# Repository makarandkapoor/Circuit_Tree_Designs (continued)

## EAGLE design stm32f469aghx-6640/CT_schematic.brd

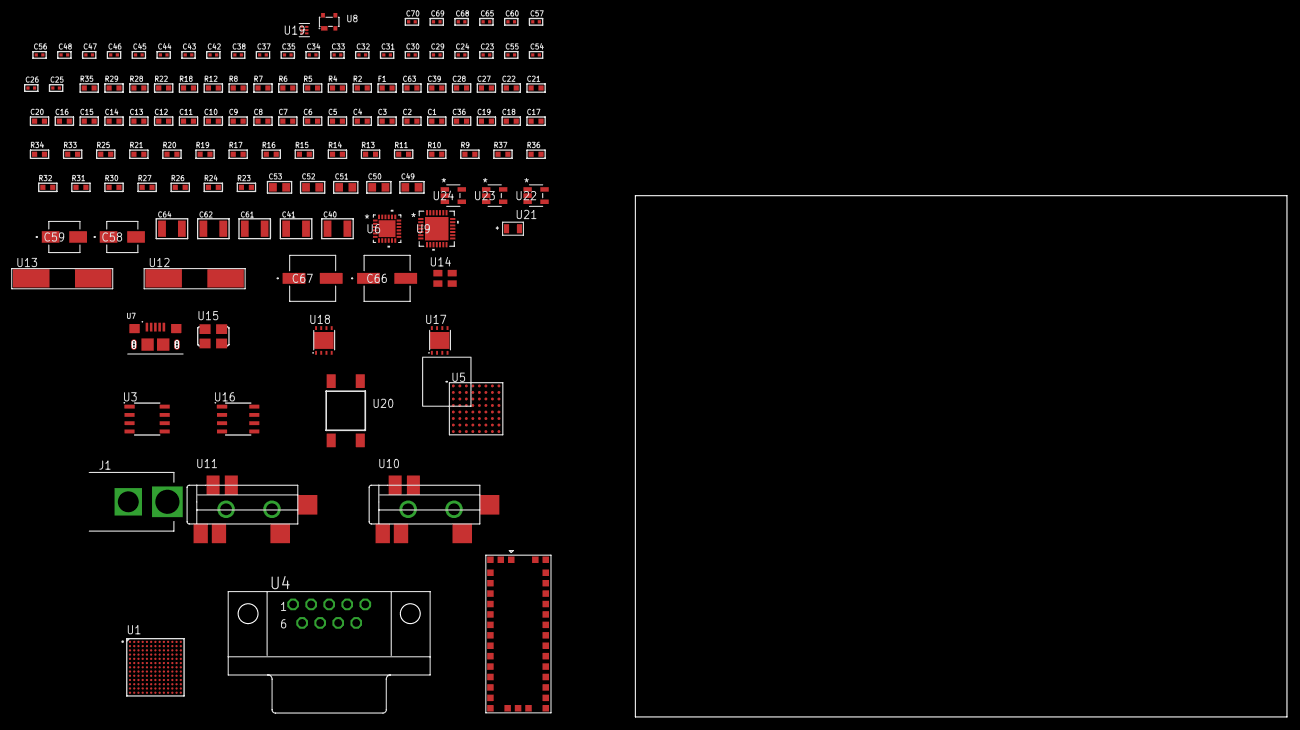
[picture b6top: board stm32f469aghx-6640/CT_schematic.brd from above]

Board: 2 copper layers, 131 parts (0 on the bottom side), 114 nets, no tracks yet.

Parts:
C1, C21, C27, C28, C39: 1e-06; C0603
C2, C3, C4, C5, C6, C7, C8, C9, C10, C11, C12, C13, C14, C15, C16, C22: 1e-07; C0603
C17: 4.7e-06; C0603
C18, C19, C36: 2.2e-06; C0603
C20: 1e-08; C0603
C23, C24: 1e-11; C0402
C25, C26, C54, C55: 2.2e-11; C0402
C29, C31, C33, C44, C45, C46, C47, C48, C65: 1e-07; C0402
C30, C32, C34, C35, C37, C38, C56, C57, C60, C68, C69, C70: 1e-08; C0402
C40, C41: 2.2e-05; C1210
C42, C43: 1e-09; C0402
C49, C50, C51, C52, C53: 1e-05; C0805
C58: 1e-06; EXV-9B
C59: 2.2e-06; EXV-9B
C61, C62, C64: 1e-05; C1210
C63: 8e-07; R0603
C66, C67: 0.0001; EXV-9H
F1: 240.0; L0603
J1: PJ-037B; PJ-037B_PACKAGE
R2, R29: 1000.0; R0603
R4, R5, R6: 4700.0; R0603
R7, R8: 2200.0; R0603
R9, R10, R11, R13, R14, R15, R16, R17, R33, R34: 10000.0; R0603
R12: 120.0; R0603
R18: 8060.0; R0603
R19, R20, R21, R25: 47000.0; R0603
R22: 680.0; R0603
R23, R24, R26, R27, R30, R32: 100000.0; R0603
R28: 2231.0; R0603
R31: 300000.0; R0603
R35: 9100.0; R0603
R36: 680000.0; R0603
R37: 120000.0; R0603
U1: STM32F469AGH6; UFBGA169
U2: M10382
U3: MCP2562-E/SN; SOIC-8
U4: 182-009-113R531; 182-009-MALE
U5: PC28F512P33BFD
U6: USB3317C-CP-TR; QFN-24
U7: 10118193-0001LF; FCI_10118193-0001LF
U8: prtr5v0u2ax; SOT143B
U9: WM8731CLSEFL; QFN-28
U10, U11: SJ-43515TS-SMT-TR
U12: ABLS-25.000MHZ-B2F-T
U13: ABLS-12.288MHZ-B4-T
U14: ASEK-32.768KHz-ECST; ASEK
U15: ASFL1-26MHZ-NCS; ASFL1
U16: LP2954AIMX/NOPB; LP2954
U17: LP3878SDX-ADJ/NOPB; WSON-8
U18: LP2951ACSDX/NOPB; WSON-8
U19: TPS3895ADRYR; SON-6
U20: 4-1437565-2; SW_4-1437565-2
U21: Q65110A2395; LGM67K-G1J2-24-Z
U22, U23, U24: nc7sz125m5x; NC7SZ125M5X

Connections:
CLK_CRYSTAL_U1_G1: C23.1, U1.G1, U12.1
CLK_CRYSTAL_U1_G2: C24.1, U1.G2, U12.2
CLK_CRYSTAL_U9_1: C54.1, U9.1, U13.1
CLK_CRYSTAL_U9_2: C55.1, U9.2, U13.2
CLK_U1_E1: U1.E1, U14.3
CLK_U6_23: U6.23, U15.3
GND: C1.2, C2.2, C3.2, C4.2, C5.2, C6.2, C7.2, C8.2, C9.2, C10.2, C11.2, C12.2, C13.2, C14.2, C15.2, C16.2, C17.2, C18.2, C19.2, C20.2, C21.2, C22.2, C23.2, C24.2, C25.2, C26.2, C27.2, C28.2, C29.2, C30.2, C31.2, C32.2, C33.2, C34.2, C35.2, C36.2, C37.2, C38.2, C39.2, C43.2, C44.2, C45.2, C46.2, C47.2, C48.2, C49.2, C50.2, C51.2, C52.2, C53.2, C54.2, C55.2, C56.2, C57.2, C58.2, C59.2, C60.2, C61.2, C62.2, C63.2, C64.2, C65.2, C66.2, C67.2, C68.2, C69.2, C70.2, J1.2, R2.2, R11.2, R18.2, R19.2, R20.2, R21.2, R26.2, R29.2, R32.2, R35.2, R37.2, U1.D11, U1.E3, U1.F5, U1.F8, U1.G7, U1.G9, U1.H11, U1.J1, U1.J2, U1.J6, U1.J7, U1.J10, U1.K11, U1.M9, U2.2, U2.4, U2.14, U2.17, U2.21, U2.24, U2.26, U2.28, U2.33, U2.34, U2.35, U2.36, U3.2, U3.8, U4.5, U5.B2, U5.H2, U5.H4, U5.H6, U6.25, U7.5, U7.6, U7.7, U7.8, U7.9, U8.1, U9.4, U9.15, U9.19, U9.25, U9.26, U9.29, U10.1, U11.1, U14.2, U15.2, U16.4, U17.3, U17.PAD, U18.3, U18.4, U18.PAD, U19.2, U21.C, U22.1, U22.3, U23.1, U23.3, U24.1, U24.3
NET_U1_A5: R10.1, U1.A5
NET_U1_C3: R9.1, U1.C3
NET_U1_C4: R8.1, U1.C4, U2.18
NET_U1_C5: R7.1, U1.C5, U2.19
NET_U1_D12: C19.1, U1.D12
NET_U1_H2: R5.1, U1.H2, U23.4
NET_U1_J3: C20.1, C21.1, F1.1, U1.J3
NET_U1_L5: R11.1, U1.L5
NET_U1_N9: C18.1, U1.N9
NET_U1_N13: U20.3, U20.4
NET_U3_6: R12.2, U3.6
NET_U4_2: R12.2, U3.6, U4.2
NET_U4_3: R12.1, U3.7, U4.3
NET_U5_A4: C33.1, C34.1, U5.A4
NET_U5_C6: R16.1, U5.C6
NET_U5_D4: R4.1, U5.D4, U22.4
NET_U6_4: C36.1, U6.4
NET_U6_22: R6.1, U6.22, U24.4
NET_U6_24: R18.1, U6.24
NET_U7_1: C39.1, U6.2, U7.1, U8.4
NET_U7_2: U6.5, U7.2, U8.3
NET_U7_3: U6.6, U7.3, U8.2
NET_U9_20: C48.1, C53.1, U9.20
NET_U10_2: C41.1, R20.1, U10.2
NET_U10_5: C40.1, R19.1, U10.5
NET_U11_5: C42.1, C43.1, R21.1, R22.1, U11.5
NET_U16_3: R24.1, U16.3
NET_U16_5: R23.1, U16.5
NET_U16_7: R25.2, R26.1, U16.7
NET_U17_1: C60.1, U17.1
NET_U17_6: R28.2, R29.1, U17.6
NET_U17_8: R27.1, U17.8
NET_U18_5: R30.1, U18.5
NET_U18_7: R31.2, R32.1, U18.7
NET_U19_1: R34.1, R35.1, U19.1
NET_U19_3: R36.2, R37.1, U19.3
NET_U19_4: R33.1, U19.4, U22.2, U23.2, U24.2
NET_U20_1: R2.1, U20.1, U20.2
PROC_CAN1_RX: U1.A13, U3.4
PROC_CAN1_TX: U1.A12, U3.1
PROC_FMC_A0: U1.F3, U5.A1
PROC_FMC_A1: U1.G3, U5.B1
PROC_FMC_A2: U1.G5, U5.C1
PROC_FMC_A3: U1.H4, U5.D1
PROC_FMC_A4: U1.L4, U5.D2
PROC_FMC_A5: U1.H3, U5.A2
PROC_FMC_A6: U1.N5, U5.C2
PROC_FMC_A7: U1.M4, U5.A3
PROC_FMC_A8: U1.H5, U5.B3
PROC_FMC_A9: U1.M6, U5.C3
PROC_FMC_A10: U1.N6, U5.D3
PROC_FMC_A11: U1.M7, U5.C4
PROC_FMC_A12: U1.F13, U5.A5
PROC_FMC_A13: U1.F12, U5.B5
PROC_FMC_A14: U1.E13, U5.C5
PROC_FMC_A15: U1.E12, U5.D7
PROC_FMC_A16: U1.M11, U5.D8
PROC_FMC_A17: U1.M13, U5.A7
PROC_FMC_A18: U1.M12, U5.B7
PROC_FMC_A19: U1.C1, U5.C7
PROC_FMC_A20: U1.C2, U5.C8
PROC_FMC_A21: U1.D1, U5.A8
PROC_FMC_A22: U1.D2, U5.G1
PROC_FMC_A23: U1.B2, U5.H8
PROC_FMC_A24: U1.A6, U5.B6
PROC_FMC_CLK: U1.C8, U5.E6
PROC_FMC_D0: U1.L12, U5.F2
PROC_FMC_D1: U1.L13, U5.E2
PROC_FMC_D2: U1.C9, U5.G3
PROC_FMC_D3: U1.C7, U5.E4
PROC_FMC_D4: U1.N7, U5.E5
PROC_FMC_D5: U1.G6, U5.G5
PROC_FMC_D6: U1.H6, U5.G6
PROC_FMC_D7: U1.H7, U5.H7
PROC_FMC_D8: U1.K7, U5.E1
PROC_FMC_D9: U1.L7, U5.E3
PROC_FMC_D10: U1.J8, U5.F3
PROC_FMC_D11: U1.K8, U5.F4
PROC_FMC_D12: U1.L8, U5.F5
PROC_FMC_D13: U1.L10, U5.H5
PROC_FMC_D14: U1.M10, U5.G7
PROC_FMC_D15: U1.L11, U5.E7
PROC_FMC_NE2: R14.1, U1.E6, U5.B4
PROC_FMC_NL: R13.1, U1.B4, U5.F6
PROC_FMC_NOE: R15.1, U1.C6, U5.F8
PROC_FMC_NWAIT: U1.D7, U5.F7
PROC_FMC_NWE: R17.1, U1.B7, U5.G8
PROC_I2S2_CK: U1.C11, U9.7
PROC_I2S2_EXT_SD: U1.B12, U9.10
PROC_I2S2_SD: U1.B10, U9.8
PROC_I2S2_WS: U1.B13, U9.9, U9.11
PROC_USB_OTG_HS_ULPI_CK: U1.M3, U6.12
PROC_USB_OTG_HS_ULPI_D0: U1.K3, U6.16
PROC_USB_OTG_HS_ULPI_D1: U1.N4, U6.15
PROC_USB_OTG_HS_ULPI_D2: U1.K5, U6.14
PROC_USB_OTG_HS_ULPI_D3: U1.M8, U6.13
PROC_USB_OTG_HS_ULPI_D4: U1.N8, U6.11
PROC_USB_OTG_HS_ULPI_D5: U1.N10, U6.10
PROC_USB_OTG_HS_ULPI_D6: U1.N11, U6.9
PROC_USB_OTG_HS_ULPI_D7: U1.D5, U6.8
PROC_USB_OTG_HS_ULPI_DIR: U1.F2, U6.19
PROC_USB_OTG_HS_ULPI_NXT: U1.M2, U6.18
PROC_USB_OTG_HS_ULPI_STP: U1.M1, U6.20
VCC_S1_12V0: C58.1, C61.1, C63.1, C66.1, C67.1, J1.1, R24.2, R27.2, U16.8, U17.4, U18.8
VCC_TIER1_1V8: C25.1, C26.1, C38.1, C44.1, C46.1, C47.1, C49.1, C51.1, C52.1, C59.1, C68.1, C69.1, C70.1, R23.2, R25.1, U2.5, U2.25, U2.27, U6.21, U9.5, U9.12, U9.18, U16.1, U22.5, U23.5, U24.5
VCC_TIER1_3V3: C1.1, C2.1, C3.1, C4.1, C5.1, C6.1, C7.1, C8.1, C9.1, C10.1, C11.1, C12.1, C13.1, C14.1, C15.1, C16.1, C17.1, C22.1, C28.1, C29.1, C30.1, C31.1, C32.1, C35.1, C37.1, C45.1, C50.1, C56.1, C57.1, C62.1, C65.1, F1.2, R4.2, R5.2, R6.2, R7.2, R8.2, R9.2, R10.2, R13.2, R14.2, R15.2, R16.2, R17.2, R28.1, R33.2, R34.2, R36.1, U1.D3, U1.D10, U1.E5, U1.F4, U1.F7, U1.G8, U1.G11, U1.J4, U1.K6, U1.K10, U1.K13, U1.L6, U1.L9, U3.5, U5.A6, U5.D5, U5.D6, U5.G4, U5.H3, U6.3, U6.17, U9.3, U14.4, U15.4, U17.5, U19.6
VCC_TIER1_5V0: C27.1, C64.1, R30.2, R31.1, U3.3, U18.1

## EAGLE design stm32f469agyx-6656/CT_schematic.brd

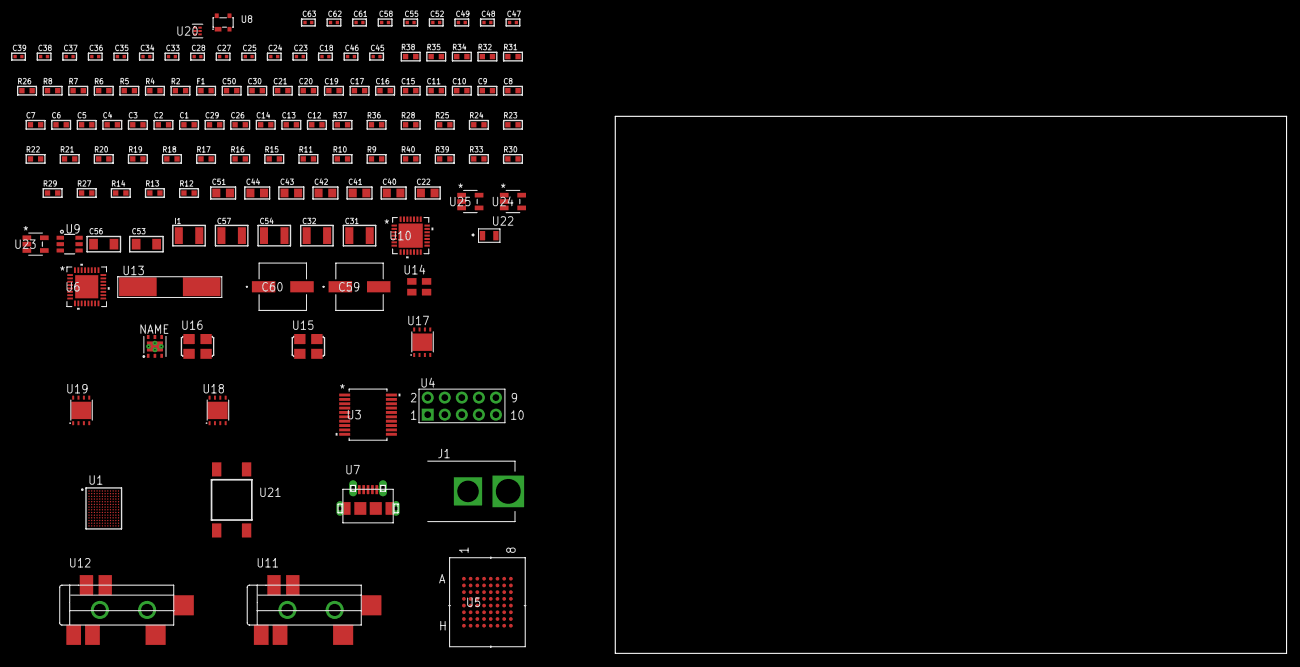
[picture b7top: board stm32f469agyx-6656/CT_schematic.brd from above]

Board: 2 copper layers, 129 parts (0 on the bottom side), 113 nets, no tracks yet.

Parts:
C1, C16, C19, C20, C21, C30, C50: 1e-06; C0603
C2, C3, C4, C5, C6, C7, C8, C9, C10, C11, C17: 1e-07; C0603
C12: 4.7e-06; C0603
C13, C14, C26, C29: 2.2e-06; C0603
C15: 1e-08; C0603
C18, C23, C24, C47, C48, C49, C52, C55, C61, C62, C63: 1e-08; C0402
C22: 4.7e-06; C0805
C25, C27, C28, C35, C36, C37, C38, C39, C58: 1e-07; C0402
C31, C32: 2.2e-05; C1210
C33, C34: 1e-09; C0402
C40, C41, C42, C43, C44, C51: 1e-05; C0805
C45, C46: 2.2e-11; C0402
C53, C56: 1e-05; C1206
C54, C57: 1e-05; C1210
C59, C60: 0.0001; EXV-9H
F1: 240.0; L0603
I1: 1.5e-05; L1210
J1: PJ-037B; PJ-037B_PACKAGE
R2, R32, R35: 1000.0; R0603
R4, R5, R6: 4700.0; R0603
R7, R8: 2200.0; R0603
R9, R10, R11, R15, R16, R17, R18, R19, R21, R22, R36, R37: 10000.0; R0603
R12, R13, R14, R27, R29, R30, R33: 100000.0; R0603
R20, R23, R24, R25: 47000.0; R0603
R26: 680.0; R0603
R28: 36000.0; R0603
R31: 2231.0; R0603
R34: 3900.0; R0603
R38: 9100.0; R0603
R39: 680000.0; R0603
R40: 120000.0; R0603
U1: STM32F469AGY6TR; WLCSP168
U2: HDC1080DMBR; WSON-6
U3: MAX3218EAP+T; SSOP-20
U4: HTSS-105-01-G-D
U5: mt28ew512aba1HPC-0AAT; LBGA-64
U6: TUSB1210BRHBR; RHB32_3P45X3P45
U7: 47590-0001; MICRO_USB_AB
U8: prtr5v0u2ax; SOT143B
U9: MAX4995AAUT+T; SOT-23-6
U10: WM8731CLSEFL; QFN-28
U11, U12: SJ-43515TS-SMT-TR
U13: ABLS-12.288MHZ-B4-T
U14: ASEK-32.768KHz-ECST; ASEK
U15: ASFL1-25MHZ-NCS; ASFL1
U16: ASFL1-26MHZ-NCS; ASFL1
U17: LP2951ACSDX/NOPB; WSON-8
U18, U19: LP3878SDX-ADJ/NOPB; WSON-8
U20: TPS3895ADRYR; SON-6
U21: 4-1437565-2; SW_4-1437565-2
U22: Q65110A2395; LGM67K-G1J2-24-Z
U23, U24, U25: nc7sz125m5x; NC7SZ125M5X

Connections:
CLK_CRYSTAL_U10_1: C45.1, U10.1, U13.1
CLK_CRYSTAL_U10_2: C46.1, U10.2, U13.2
CLK_U1_E11: U1.E11, U14.3
CLK_U1_K11: U1.K11, U15.3
CLK_U6_1: U6.1, U16.3
GND: C1.2, C2.2, C3.2, C4.2, C5.2, C6.2, C7.2, C8.2, C9.2, C10.2, C11.2, C12.2, C13.2, C14.2, C15.2, C16.2, C17.2, C18.2, C19.2, C20.2, C21.2, C23.2, C24.2, C25.2, C26.2, C27.2, C28.2, C29.2, C30.2, C34.2, C35.2, C36.2, C37.2, C38.2, C39.2, C40.2, C41.2, C42.2, C43.2, C44.2, C45.2, C46.2, C47.2, C48.2, C49.2, C50.2, C51.2, C52.2, C53.2, C54.2, C55.2, C56.2, C57.2, C58.2, C59.2, C60.2, C61.2, C62.2, C63.2, J1.2, R2.2, R20.2, R23.2, R24.2, R25.2, R29.2, R32.2, R35.2, R38.2, R40.2, U1.A4, U1.B7, U1.B10, U1.C1, U1.F2, U1.F12, U1.H1, U1.H7, U1.J11, U1.L11, U1.M1, U1.N8, U1.N11, U1.P4, U2.2, U2.PAD, U3.5, U3.17, U3.20, U4.9, U5.E8, U5.H2, U5.H7, U6.33, U7.5, U7.6, U7.7, U7.8, U7.9, U8.1, U9.2, U10.4, U10.15, U10.19, U10.25, U10.26, U10.29, U11.1, U12.1, U14.2, U15.2, U16.2, U17.3, U17.4, U17.PAD, U18.3, U18.PAD, U19.3, U19.PAD, U20.2, U22.C, U23.1, U23.3, U24.1, U24.3, U25.1, U25.3
NET_U1_A9: R8.1, U1.A9, U2.1
NET_U1_B9: R7.1, U1.B9, U2.6
NET_U1_D2: C14.1, U1.D2
NET_U1_D9: R9.1, U1.D9
NET_U1_F8: R10.1, U1.F8
NET_U1_H9: R5.1, U1.H9, U24.4
NET_U1_M12: C15.1, C16.1, F1.1, U1.M12
NET_U1_N4: C13.1, U1.N4
NET_U1_P9: R11.1, U1.P9
NET_U1_P11: U21.3, U21.4
NET_U3_1: I1.1, U3.1
NET_U3_2: R12.1, U3.2
NET_U3_3: R13.1, U3.3
NET_U3_4: R14.1, U3.4
NET_U3_15: C21.1, U3.15
NET_U3_16: C22.2, U3.16
NET_U3_18: C22.1, U3.18
NET_U3_19: C20.1, U3.19
NET_U4_3: U3.12, U4.3
NET_U4_4: U3.11, U4.4
NET_U4_5: U3.14, U4.5
NET_U4_6: U3.13, U4.6
NET_U5_B4: R18.1, U5.B4
NET_U5_B5: R4.1, U5.B5, U23.4
NET_U6_11: R21.1, U6.11
NET_U6_12: C29.1, U6.12
NET_U6_14: R22.1, U6.14
NET_U6_20: C26.1, U6.20
NET_U6_27: R6.1, U6.27, U25.4
NET_U7_1: C30.1, U6.22, U7.1, U8.4, U9.1
NET_U7_2: U6.19, U7.2, U8.3
NET_U7_3: U6.18, U7.3, U8.2
NET_U7_4: U6.23, U7.4
NET_U9_3: R20.1, U9.3
NET_U9_4: U6.17, U9.4
NET_U10_20: C39.1, C44.1, U10.20
NET_U11_2: C32.1, R24.1, U11.2
NET_U11_5: C31.1, R23.1, U11.5
NET_U12_5: C33.1, C34.1, R25.1, R26.1, U12.5
NET_U17_5: R27.1, U17.5
NET_U17_7: R28.2, R29.1, U17.7
NET_U18_1: C52.1, U18.1
NET_U18_6: R31.2, R32.1, U18.6
NET_U18_8: R30.1, U18.8
NET_U19_1: C55.1, U19.1
NET_U19_6: R34.2, R35.1, U19.6
NET_U19_8: R33.1, U19.8
NET_U20_1: R37.1, R38.1, U20.1
NET_U20_3: R39.2, R40.1, U20.3
NET_U20_4: R36.1, U20.4, U23.2, U24.2, U25.2
NET_U21_1: R2.1, U21.1, U21.2
PROC_FMC_A0: U1.G10, U5.E2
PROC_FMC_A1: U1.H10, U5.D2
PROC_FMC_A2: U1.G12, U5.C2
PROC_FMC_A3: U1.H11, U5.A2
PROC_FMC_A4: U1.J10, U5.B2
PROC_FMC_A5: U1.H12, U5.D3
PROC_FMC_A6: U1.M8, U5.C3
PROC_FMC_A7: U1.J7, U5.A3
PROC_FMC_A8: U1.L7, U5.B6
PROC_FMC_A9: U1.H8, U5.A6
PROC_FMC_A10: U1.J6, U5.C6
PROC_FMC_A11: U1.P7, U5.D6
PROC_FMC_A12: U1.G5, U5.B7
PROC_FMC_A13: U1.G4, U5.A7
PROC_FMC_A14: U1.G2, U5.C7
PROC_FMC_A15: U1.G1, U5.D7
PROC_FMC_A16: U1.J4, U5.E7
PROC_FMC_A17: U1.M2, U5.B3
PROC_FMC_A18: U1.H4, U5.C4
PROC_FMC_A19: U1.E10, U5.D5
PROC_FMC_A20: U1.C11, U5.D4
PROC_FMC_A21: U1.B12, U5.C5
PROC_FMC_A22: U1.D11, U5.B8
PROC_FMC_A23: U1.F9, U5.C8
PROC_FMC_A24: U1.E8, U5.F8
PROC_FMC_D0: U1.L3, U5.E3
PROC_FMC_D1: U1.L2, U5.H3
PROC_FMC_D2: U1.E6, U5.E4
PROC_FMC_D3: U1.A3, U5.H4
PROC_FMC_D4: U1.N7, U5.H5
PROC_FMC_D5: U1.M7, U5.E5
PROC_FMC_D6: U1.K6, U5.H6
PROC_FMC_D7: U1.P6, U5.E6
PROC_FMC_D8: U1.N6, U5.F3
PROC_FMC_D9: U1.M6, U5.G3
PROC_FMC_D10: U1.L6, U5.F4
PROC_FMC_D11: U1.J5, U5.G4
PROC_FMC_D12: U1.P5, U5.F5
PROC_FMC_D13: U1.L4, U5.G6
PROC_FMC_D14: U1.N1, U5.F6
PROC_FMC_D15: U1.M3, U5.G7
PROC_FMC_NBL0: R19.1, U1.A10, U5.F7
PROC_FMC_NE2: R15.1, U1.D7, U5.F2
PROC_FMC_NOE: R16.1, U1.B4, U5.G2
PROC_FMC_NWAIT: U1.E7, U5.A4
PROC_FMC_NWE: R17.1, U1.C6, U5.A5
PROC_I2S2_CK: U1.C3, U10.7
PROC_I2S2_EXT_SD: U1.A1, U10.10
PROC_I2S2_SD: U1.B2, U10.8
PROC_I2S2_WS: U1.E5, U10.9, U10.11
PROC_UART4_RX: U1.B3, U3.9
PROC_UART4_TX: U1.D5, U3.7
VCC_S1_7V1: C50.1, C53.1, C56.1, C59.1, C60.1, J1.1, R30.2, R33.2, U17.8, U18.4, U19.4
VCC_TIER1_1V8: C25.1, C27.1, C28.1, C35.1, C37.1, C38.1, C40.1, C42.1, C43.1, C51.1, C61.1, C62.1, C63.1, R6.2, R21.2, R22.2, R27.2, R28.1, U6.21, U6.28, U6.30, U6.32, U10.5, U10.12, U10.18, U17.1, U23.5, U24.5, U25.5
VCC_TIER1_3V3: C1.1, C2.1, C3.1, C4.1, C5.1, C6.1, C7.1, C8.1, C9.1, C10.1, C11.1, C12.1, C17.1, C18.1, C19.1, C23.1, C24.1, C36.1, C41.1, C47.1, C48.1, C49.1, C54.1, C58.1, F1.2, I1.2, R4.2, R5.2, R7.2, R8.2, R9.2, R10.2, R11.2, R12.2, R13.2, R14.2, R15.2, R16.2, R17.2, R18.2, R19.2, R31.1, R36.2, R37.2, R39.1, U1.A7, U1.A11, U1.B5, U1.C2, U1.C12, U1.F1, U1.G11, U1.J12, U1.L1, U1.P3, U1.P8, U1.P12, U2.5, U3.6, U5.D8, U5.F1, U5.G5, U10.3, U14.4, U15.4, U16.4, U18.5, U20.6
VCC_TIER1_5V0: C57.1, R34.1, U9.5, U19.5

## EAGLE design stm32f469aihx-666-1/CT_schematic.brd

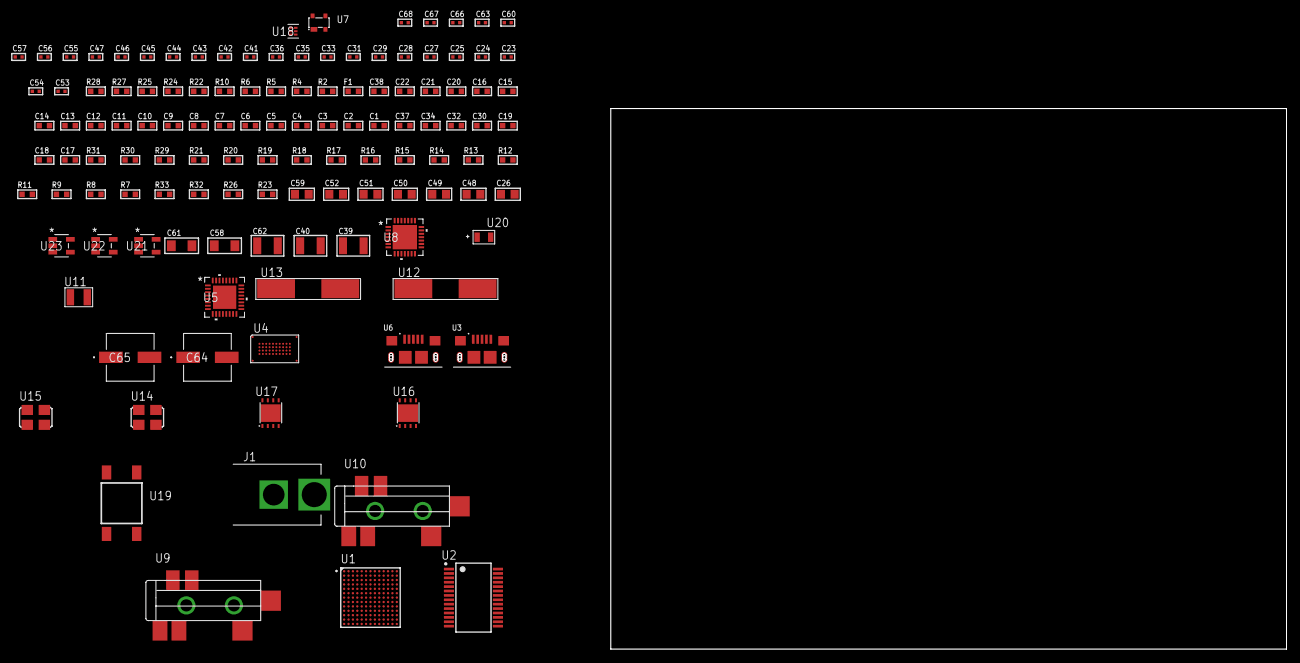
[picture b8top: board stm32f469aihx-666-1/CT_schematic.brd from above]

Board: 2 copper layers, 124 parts (0 on the bottom side), 97 nets, no tracks yet.

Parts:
C1, C21, C38: 1e-06; C0603
C2, C3, C4, C5, C6, C7, C8, C9, C10, C11, C12, C13, C14, C15, C16, C22: 1e-07; C0603
C17: 4.7e-06; C0603
C18, C19, C30, C32, C34, C37: 2.2e-06; C0603
C20: 1e-08; C0603
C23, C24: 1e-11; C0402
C25, C27, C28, C29, C31, C33, C35, C36, C43, C44, C45, C46, C47, C63: 1e-07; C0402
C26: 4.7e-06; C0805
C39, C40: 2.2e-05; C1210
C41, C42: 1e-09; C0402
C48, C49, C50, C51, C52, C59: 1e-05; C0805
C53, C54: 2.2e-11; C0402
C55, C56, C57, C60, C66, C67, C68: 1e-08; C0402
C58, C61: 1e-05; C1206
C62: 1e-05; C1210
C64, C65: 0.0001; EXV-9H
F1: 240.0; L0603
J1: PJ-037B; PJ-037B_PACKAGE
R2, R25, R28: 1000.0; R0603
R4, R5, R6, R10: 4700.0; R0603
R7, R8, R9, R11, R12, R13, R14, R15, R16, R17, R18, R29, R30: 10000.0; R0603
R19, R20, R21: 47000.0; R0603
R22: 680.0; R0603
R23, R26: 100000.0; R0603
R24: 806.0; R0603
R27: 2231.0; R0603
R31: 82000.0; R0603
R32: 300000.0; R0603
R33: 120000.0; R0603
U1: STM32F469AIH6; UFBGA169
U2: FT232RL-REEL; SSOP-28
U3, U6: 10118193-0001LF; FCI_10118193-0001LF
U4: S29VS256RABBHW000
U5: TUSB1210BRHBR; RHB32_3P45X3P45
U7: prtr5v0u2ax; SOT143B
U8: WM8731CLSEFL; QFN-28
U9, U10: SJ-43515TS-SMT-TR
U11: ABS07-32.768KHZ-7-T
U12: ABLS-12.000MHZ-B4-T
U13: ABLS-12.288MHZ-B4-T
U14: ASFL1-19.2MHZ-NCS; ASFL1
U15: ASFL1-25MHZ-NCS; ASFL1
U16, U17: LP3878SDX-ADJ/NOPB; WSON-8
U18: TPS3895ADRYR; SON-6
U19: 4-1437565-2; SW_4-1437565-2
U20: Q65110A2395; LGM67K-G1J2-24-Z
U21, U22, U23: nc7sz125m5x; NC7SZ125M5X

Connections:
CLK_CRYSTAL_U1_E1: C23.1, U1.E1, U11.1
CLK_CRYSTAL_U1_F1: C24.1, U1.F1, U11.2
CLK_CRYSTAL_U2_27: U2.27, U12.1
CLK_CRYSTAL_U2_28: U2.28, U12.2
CLK_CRYSTAL_U8_1: C53.1, U8.1, U13.1
CLK_CRYSTAL_U8_2: C54.1, U8.2, U13.2
CLK_U1_G2: U1.G2, U15.3
CLK_U5_1: U5.1, U14.3
GND: C1.2, C2.2, C3.2, C4.2, C5.2, C6.2, C7.2, C8.2, C9.2, C10.2, C11.2, C12.2, C13.2, C14.2, C15.2, C16.2, C17.2, C18.2, C19.2, C20.2, C21.2, C22.2, C23.2, C24.2, C25.2, C26.2, C27.2, C28.2, C29.2, C30.2, C31.2, C32.2, C33.2, C34.2, C35.2, C36.2, C37.2, C38.2, C42.2, C43.2, C44.2, C45.2, C46.2, C47.2, C48.2, C49.2, C50.2, C51.2, C52.2, C53.2, C54.2, C55.2, C56.2, C57.2, C58.2, C59.2, C60.2, C61.2, C62.2, C63.2, C64.2, C65.2, C66.2, C67.2, C68.2, J1.2, R2.2, R12.2, R18.2, R19.2, R20.2, R21.2, R25.2, R28.2, R31.2, R33.2, U1.D11, U1.E3, U1.F5, U1.F8, U1.G7, U1.G9, U1.H11, U1.J1, U1.J2, U1.J6, U1.J7, U1.J10, U1.K11, U1.M9, U2.7, U2.18, U2.21, U2.25, U2.26, U3.5, U3.6, U3.7, U3.8, U3.9, U4.C5, U4.D12, U4.E3, U4.F5, U5.33, U6.5, U6.6, U6.7, U6.8, U6.9, U7.1, U8.4, U8.15, U8.19, U8.25, U8.26, U8.29, U9.1, U10.1, U14.2, U15.2, U16.3, U16.PAD, U17.3, U17.PAD, U18.2, U20.C, U21.1, U21.3, U22.1, U22.3, U23.1, U23.3
NET_U1_A5: R8.1, U1.A5
NET_U1_C3: R7.1, U1.C3
NET_U1_D12: C19.1, U1.D12
NET_U1_H2: R5.1, U1.H2, U22.4
NET_U1_J3: C20.1, C21.1, F1.1, U1.J3
NET_U1_L5: R9.1, U1.L5
NET_U1_N9: C18.1, U1.N9
NET_U1_N13: U19.3, U19.4
NET_U2_14: R11.1, U2.14
NET_U2_17: C27.1, U2.17
NET_U2_19: R12.1, U2.19
NET_U3_1: R10.1, U3.1
NET_U3_2: U2.16, U3.2
NET_U3_3: U2.15, U3.3
NET_U4_D8: R4.1, U4.D8, U21.4
NET_U5_11: R17.1, U5.11
NET_U5_12: C37.1, U5.12
NET_U5_14: R18.1, U5.14
NET_U5_20: C34.1, U5.20
NET_U5_27: R6.1, U5.27, U23.4
NET_U6_1: C38.1, U5.22, U6.1, U7.4
NET_U6_2: U5.19, U6.2, U7.3
NET_U6_3: U5.18, U6.3, U7.2
NET_U8_20: C47.1, C52.1, U8.20
NET_U9_2: C40.1, R20.1, U9.2
NET_U9_5: C39.1, R19.1, U9.5
NET_U10_5: C41.1, C42.1, R21.1, R22.1, U10.5
NET_U16_1: C57.1, U16.1
NET_U16_6: R24.2, R25.1, U16.6
NET_U16_8: R23.1, U16.8
NET_U17_1: C60.1, U17.1
NET_U17_6: R27.2, R28.1, U17.6
NET_U17_8: R26.1, U17.8
NET_U18_1: R30.1, R31.1, U18.1
NET_U18_3: R32.2, R33.1, U18.3
NET_U18_4: R29.1, U18.4, U21.2, U22.2, U23.2
NET_U19_1: R2.1, U19.1, U19.2
PROC_FMC_A16: U1.M11, U4.D4
PROC_FMC_A17: U1.M13, U4.C11
PROC_FMC_A18: U1.M12, U4.D10
PROC_FMC_A19: U1.C1, U4.C10
PROC_FMC_A20: U1.C2, U4.D5
PROC_FMC_A21: U1.D1, U4.C4
PROC_FMC_A22: U1.D2, U4.C12
PROC_FMC_A23: U1.B2, U4.D7
PROC_FMC_CLK: U1.C8, U4.C6
PROC_FMC_D0: U1.L12, U4.F3
PROC_FMC_D1: U1.L13, U4.F4
PROC_FMC_D2: U1.C9, U4.E6
PROC_FMC_D3: U1.C7, U4.E7
PROC_FMC_D4: U1.N7, U4.F8
PROC_FMC_D5: U1.G6, U4.F9
PROC_FMC_D6: U1.H6, U4.E10
PROC_FMC_D7: U1.H7, U4.E11
PROC_FMC_D8: U1.K7, U4.E4
PROC_FMC_D9: U1.L7, U4.E5
PROC_FMC_D10: U1.J8, U4.F6
PROC_FMC_D11: U1.K8, U4.F7
PROC_FMC_D12: U1.L8, U4.E8
PROC_FMC_D13: U1.L10, U4.E9
PROC_FMC_D14: U1.M10, U4.F11
PROC_FMC_D15: U1.L11, U4.F12
PROC_FMC_NE2: R14.1, U1.E6, U4.D11
PROC_FMC_NL: U1.B4, U4.D6
PROC_FMC_NOE: R16.1, U1.C6, U4.E12
PROC_FMC_NWAIT: R13.1, U1.D7, U4.C3
PROC_FMC_NWE: R15.1, U1.B7, U4.C8
PROC_I2S2_CK: U1.C11, U8.7
PROC_I2S2_EXT_SD: U1.B12, U8.10
PROC_I2S2_SD: U1.B10, U8.8
PROC_I2S2_WS: U1.B13, U8.9, U8.11
PROC_UART4_RX: U1.B9, U2.1
PROC_UART4_TX: U1.C10, U2.5
PROC_USB_OTG_HS_ULPI_CK: U1.M3, U5.26
PROC_USB_OTG_HS_ULPI_D0: U1.K3, U5.3
PROC_USB_OTG_HS_ULPI_D1: U1.N4, U5.4
PROC_USB_OTG_HS_ULPI_D2: U1.K5, U5.5
PROC_USB_OTG_HS_ULPI_D3: U1.M8, U5.6
PROC_USB_OTG_HS_ULPI_D4: U1.N8, U5.7
PROC_USB_OTG_HS_ULPI_D5: U1.N10, U5.9
PROC_USB_OTG_HS_ULPI_D6: U1.N11, U5.10
PROC_USB_OTG_HS_ULPI_D7: U1.D5, U5.13
PROC_USB_OTG_HS_ULPI_DIR: U1.F2, U5.31
PROC_USB_OTG_HS_ULPI_NXT: U1.M2, U5.2
PROC_USB_OTG_HS_ULPI_STP: U1.M1, U5.29
VCC_S1_9V4: C58.1, C61.1, C64.1, C65.1, J1.1, R23.2, R26.2, U16.4, U17.4
VCC_TIER1_1V8: C1.1, C2.1, C3.1, C4.1, C5.1, C6.1, C7.1, C8.1, C9.1, C10.1, C11.1, C12.1, C13.1, C14.1, C15.1, C16.1, C17.1, C28.1, C29.1, C30.1, C31.1, C32.1, C35.1, C36.1, C43.1, C44.1, C45.1, C46.1, C48.1, C49.1, C50.1, C51.1, C59.1, C63.1, C66.1, C67.1, C68.1, F1.2, R4.2, R5.2, R6.2, R7.2, R8.2, R9.2, R13.2, R14.2, R15.2, R16.2, R17.2, R24.1, R29.2, R30.2, R32.1, U1.D3, U1.D10, U1.E5, U1.F4, U1.F7, U1.G8, U1.J4, U1.K6, U1.K10, U1.K13, U1.L6, U1.L9, U2.4, U4.C7, U4.D3, U4.F10, U5.28, U5.30, U5.32, U8.3, U8.5, U8.12, U8.18, U16.5, U18.6, U21.5, U22.5, U23.5
VCC_TIER1_3V3: C22.1, C25.1, C26.1, C33.1, C55.1, C56.1, C62.1, R11.2, R27.1, U1.G11, U2.20, U5.21, U14.4, U15.4, U17.5
